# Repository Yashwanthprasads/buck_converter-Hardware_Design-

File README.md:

# buck_converter-Hardware_Design-
Buck converter make using kicad 9.0

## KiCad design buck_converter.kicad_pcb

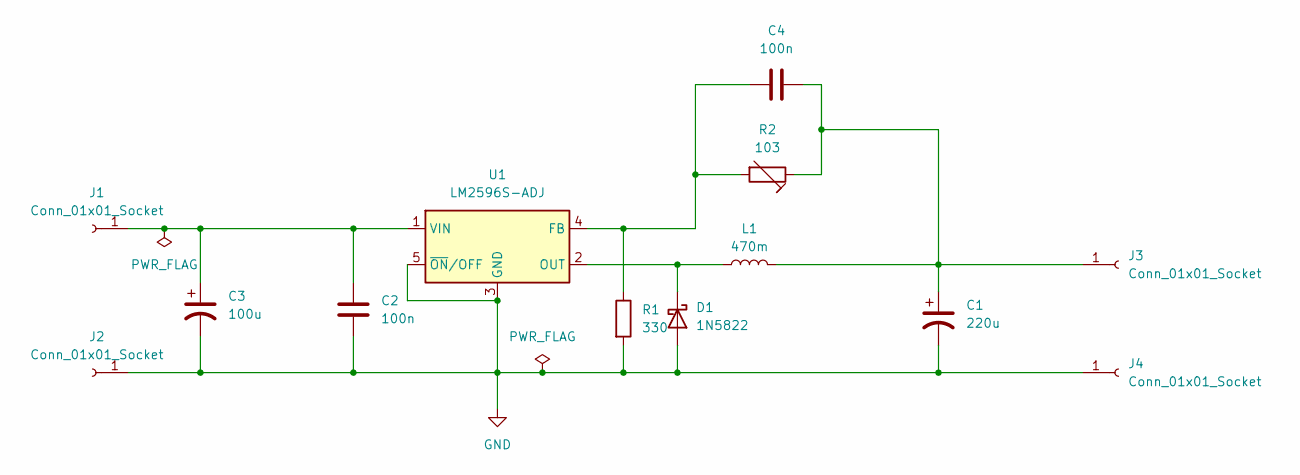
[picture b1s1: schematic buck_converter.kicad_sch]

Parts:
C1: 220u; CP_Elec_8x10
C2, C4: 100n; C_0603_1608Metric_Pad1.08x0.95mm_HandSolder
C3: 100u; CP_Elec_8x10
D1: 1N5822; D_1206_3216Metric
J1, J2, J3, J4: Conn_01x01_Socket; SolderWire-0.5sqmm_1x01_D0.9mm_OD2.1mm
L1: 470m; L_12x12mm_H8mm
R1: 330; R_0603_1608Metric_Pad0.98x0.95mm_HandSolder
R2: 103; Potentiometer_Bourns_3296Y_Vertical
U1: LM2596S-ADJ; TO-263-5_TabPin3

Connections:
GND: C1.2, C2.2, C3.2, D1.2 (A), J2.1, J4.1, R1.2, U1.3 (GND), U1.5 (~ON/OFF)
unnamed: D1.1 (K), L1.1, U1.2 (OUT)
unnamed: C2.1, C3.1, J1.1, U1.1 (VIN)
unnamed: C1.1, C4.2, J3.1, L1.2, R2.1
unnamed: C4.1, R1.1, R2.2, U1.4 (FB)

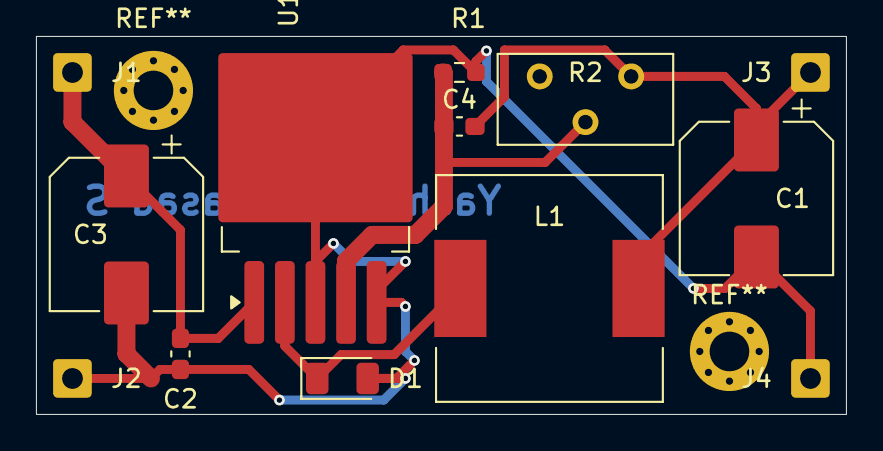
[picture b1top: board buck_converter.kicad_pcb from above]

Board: 2 copper layers, 45.0 x 21.0 mm, 13 parts (0 on the bottom side), 5 nets.
